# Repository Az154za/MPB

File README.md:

# MPB

MPB is a modular diy power bank that is 100% scalable it does have batterie protection leds to show charging status 
Keep in mind that this project is still work in progress it lacks some ideas 

# BOM ( Bill of Material )
- USB C receptacle
- two Leds 
- ten 1x02 pinHeaders
- two Nmos transistors
- five capacitors
- a tp4056
- DW0A1
-  one voltage regulator BD33FC0WFP
-  ten resistors
# PCB and schematic
this is the schematic :

this is the pcb routing :

and finally this is the 3D overview of the pcb:

I hope you like the idea of the project.
any suggestions are welcomed

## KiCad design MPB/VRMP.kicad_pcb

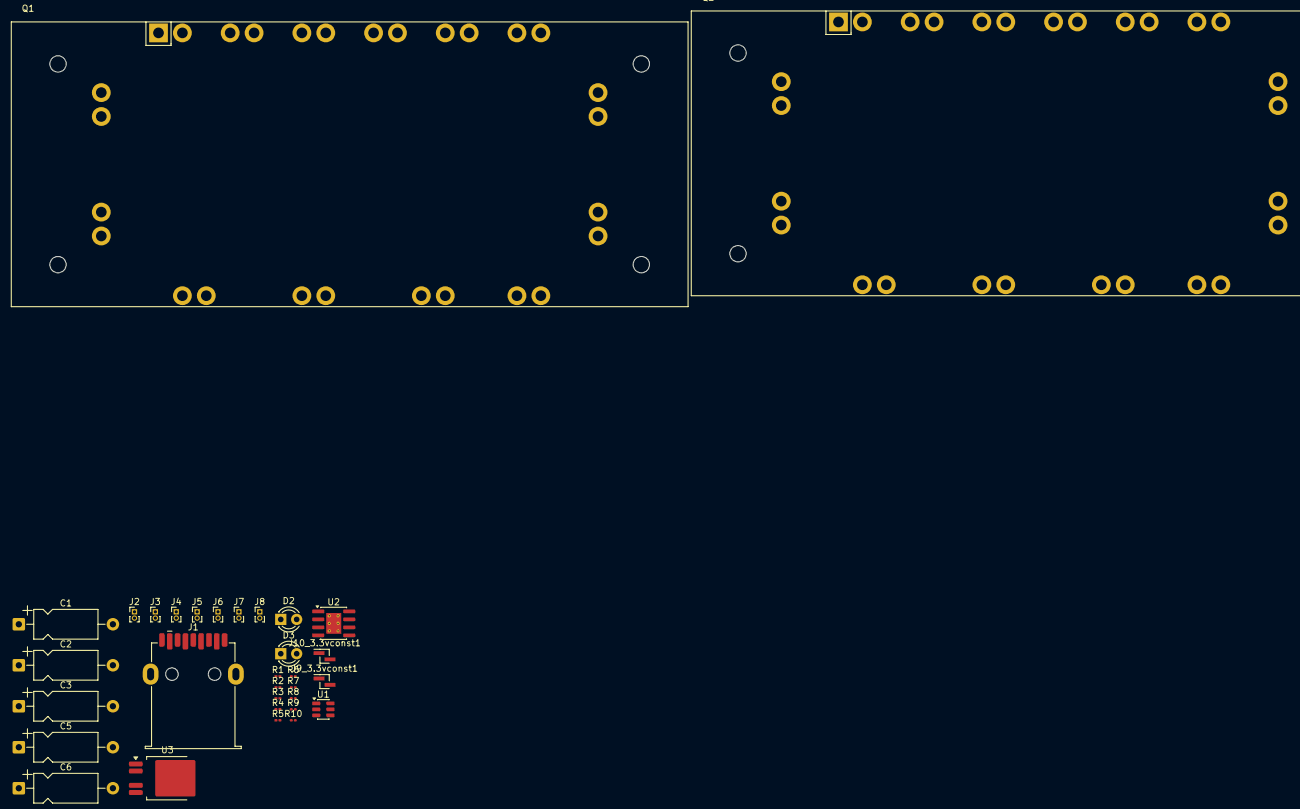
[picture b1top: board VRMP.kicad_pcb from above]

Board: 2 copper layers, 32 parts (0 on the bottom side), 15 nets, no tracks yet.

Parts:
C1: 0.1uF; CP_Axial_L10.0mm_D4.5mm_P15.00mm_Horizontal
C2, C5, C6: 10uF; CP_Axial_L10.0mm_D4.5mm_P15.00mm_Horizontal
C3: 22uF; CP_Axial_L10.0mm_D4.5mm_P15.00mm_Horizontal
D2, D3: LED; LED_D3.0mm
J1: USB_C_Receptacle_USB2.0_14P; USB3_A_Receptacle_Wuerth_692122030100
J2, J3, J4, J5, J6, J7, J8: Conn_01x02_Socket; PinHeader_1x02_P1.00mm_Vertical
J9_3.3vconst1, J10_3.3vconst1: Conn_01x02_Socket; PinHeader_1x02_P1.00mm_Vertical_SMD_Pin1Left
Q1, Q2: NMOS; Infineon_AG-ECONO2
R1, R2: 5.1k; R_0201_0603Metric
R3, R4, R5, R6, R7, R10: 1k; R_0201_0603Metric
R8: 200; R_0201_0603Metric
R9: 100; R_0201_0603Metric
U1: DW01A; SOT-23-6
U2: TP4056-42-ESOP8; SOIC-8-1EP_3.9x4.9mm_P1.27mm_EP2.41x3.3mm_ThermalVias
U3: BD33FC0WFP; TO-252-4

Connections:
+: C1.1, C2.1, J2.1, J3.1, J4.1, J5.1, J6.1, J7.1, J8.1, R9.1, U1.5 (VCC), U3.2 (VCC)
-: J2.2, J3.2, J4.2, J5.2, J6.2, J7.2, J8.2, J9_3.3vconst1.2, J10_3.3vconst1.2, Q2.3 (S), R10.1
GND: C1.2, C2.2, C3.2, C5.1, C5.2, C6.2, D2.2 (A), D3.2 (A), Q1.3 (S), R1.2, R2.2, R5.1, R6.1, R7.1, R8.1, R8.2, U1.6 (GND), U2.3 (GND), U2.4 (V_{CC}), U2.8 (CE), U3.3 (GND)
unnamed: D2.1 (K), R4.1
unnamed: D3.1 (K), R3.1
unnamed: C3.1, J9_3.3vconst1.1, J10_3.3vconst1.1, U3.4 (VO)
unnamed: Q1.1 (D), Q2.1 (D)
unnamed: Q1.2 (G), U1.1 (OD)
unnamed: Q2.2 (G), U1.3 (OC)
unnamed: R10.2, U1.2 (CS)
unnamed: C6.1, R9.2, U2.5 (BAT)
unnamed: R5.2, U2.2 (PROG)
unnamed: R6.2, U2.1 (TEMP)
unnamed: R4.2, U2.7 (~CHRG)
unnamed: R3.2, U2.6 (~STDBY)
